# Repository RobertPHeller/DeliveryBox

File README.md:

# Delivery Box -- A lockable box for delivery prople to deliver stuff to.

This is a design for a delivery box -- a lockable box that delivery drivers
can place deliveries into, using one-time codes, where the delivery can be 
securely  housed  until the resident can retrieve  them.  This is to allow for
secure deliveries when noone is home to receive them.  The box will be
lockable and can be secured.  This will make deliveries secure from 
"porch pirates".

- [BoxDesign](BoxDesign/)

- [Circuit](Circuit/)

- [Firmware](DeliveryBoxFirmware/)

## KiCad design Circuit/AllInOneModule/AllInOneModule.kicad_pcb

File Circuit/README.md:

# This is the circuit design

The circuit design uses these parts: 

1. A main board containing an Adafruit ESP32-S3 Feather and connection headers
for a servo  and the  keypad  (there is a  STEMMA/QWIC  connector  for the I2C
connection to the Display Module on th Feather board).  The Adafruit  ESP32-S3
Feather  includes a JST battery  connection and includes a LiPo battery charge
circuit.

2.  A  display  module  with  a  HT16K33   breakout  and  4  dual   14-segment
alphanumberic display modules.

3.  A 12-key keypad board.

4. A high torque metal gear servo will be used to operate a lock.

5. A LiPo battery

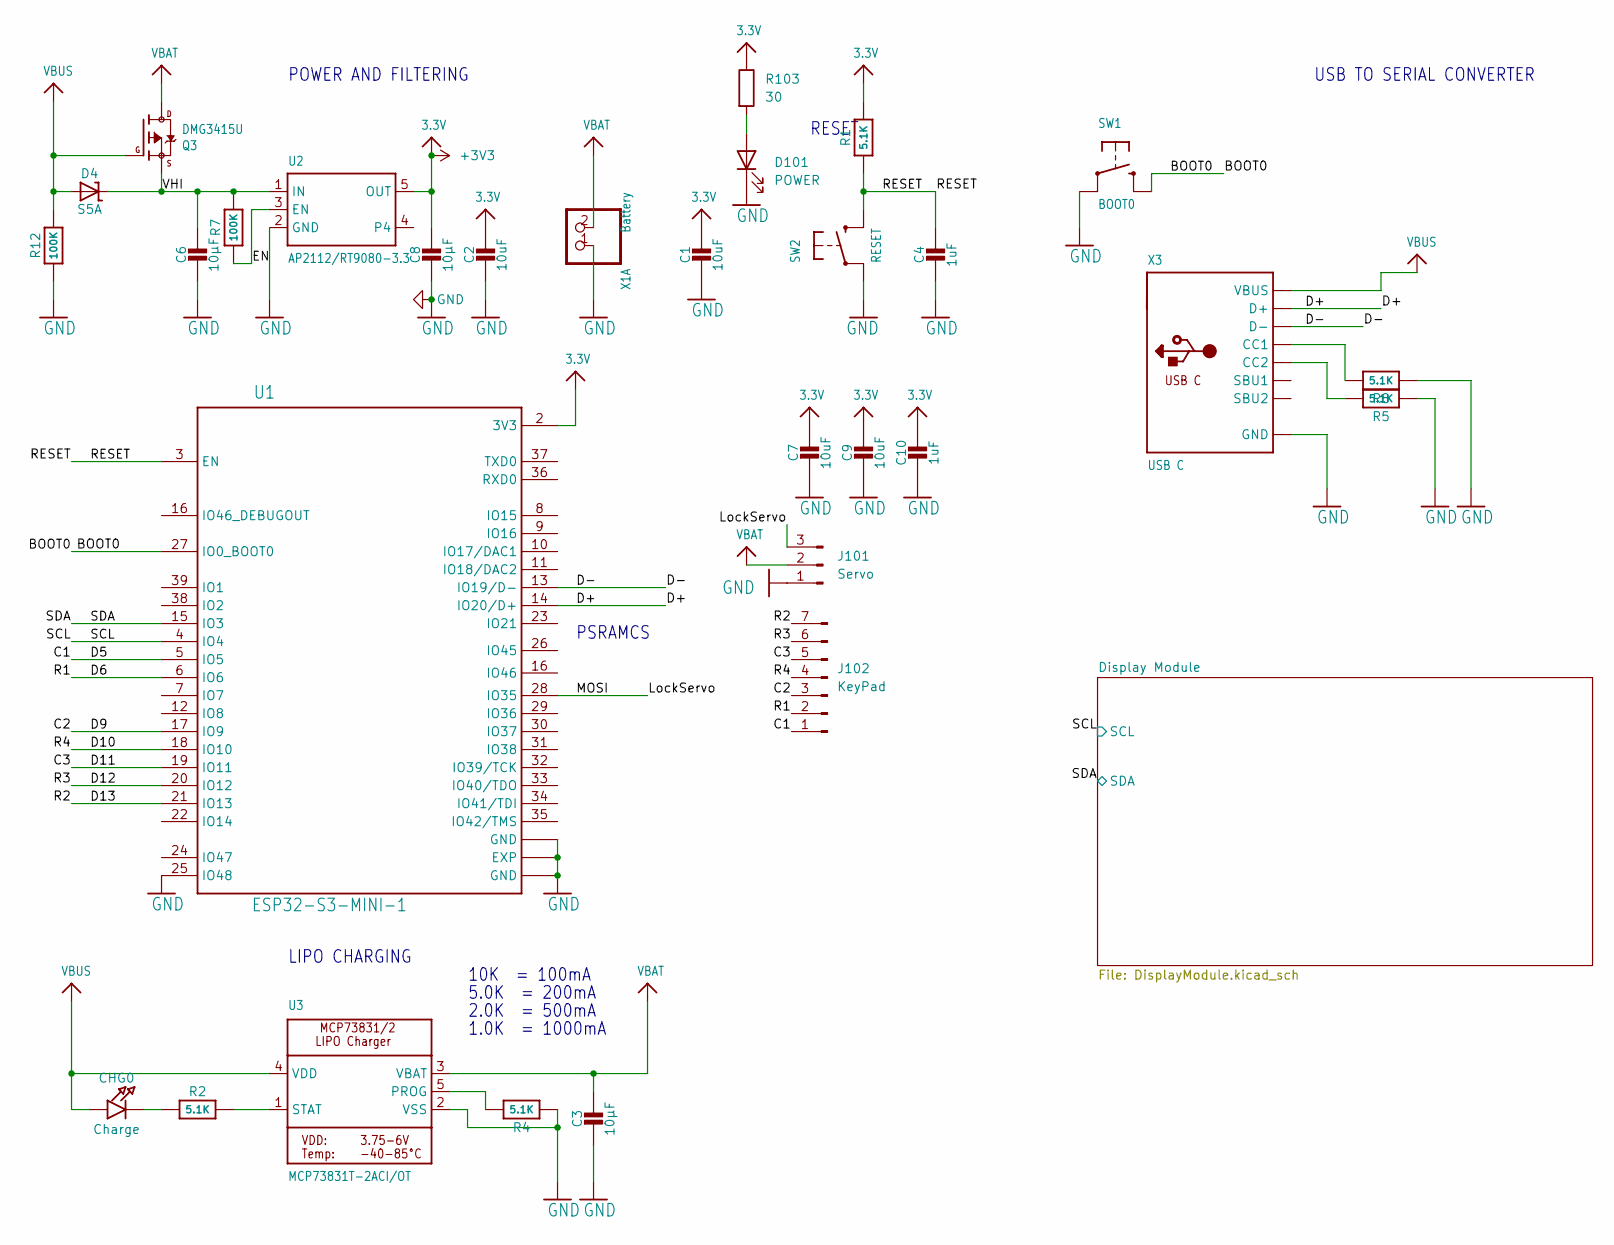
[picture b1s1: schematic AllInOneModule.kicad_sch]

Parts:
C1, C2, C7, C9: 10uF; C_0805_2012Metric; Mouser Part Number 187-CL21A106KQFNFNE
C3, C6, C8: 10µF; C_0805_2012Metric; Mouser Part Number 187-CL21A106KQFNFNE
C4, C10: 1uF; C_0603_1608Metric; Mouser Part Number 80-C0603C105K9PLR
CHG0: Charge; LED_0603_1608Metric; Mouser Part Number 859-LTST-C190KFKT
D4: S5A; S5AE357T; Mouser Part Number 637-S5A
D101: POWER; LED_0603_1608Metric; Mouser Part Number 604-AA1608ZGSK10MAV
J101: Servo; PinHeader_1x03_P2.54mm_Horizontal
J102: KeyPad; PinHeader_1x07_P2.54mm_Horizontal
Q3: DMG3415U; SOT-23-3; Mouser Part Number 621-DMG3415U-7
R1, R2, R4, R5, R8: 5.1K; R_0603_1608Metric; Mouser Part Number 603-RC0603JR-075K1P
R7, R12: 100K; R_0603_1608Metric; Mouser Part Number 603-RT0603DRD07100KL
R103: 30; R_0603_1608Metric; Mouser Part Number 603-AC0603JR-0730RL
SW1: BOOT0; SW_Push_1P1T_NO_CK_KMR2; Mouser Part Number 611-KMR211NGLFS
SW2: RESET; SW_Push_1P1T_NO_CK_KMR2; Mouser Part Number 611-KMR211NGLFS
U1: ESP32-S3-MINI-1; ESP32_S3_WROOM-1; Mouser Part Number 356-ESP32-S3-MINI1N8
U2: AP2112/RT9080-3.3; SOT-23-5; Mouser Part Number 621-AP2112K-3.3TRG1
U3: MCP73831T-2ACI/OT; SOT-23-5; Mouser Part Number 579-MCP73831T-2ACIOT
X1: Battery; JST_PH_S2B-PH-SM4-TB_1x02-1MP_P2.00mm_Horizontal; Mouser Part Number 306-S2BPHSM4TBLFSN
X3: USB C; CONN_USB4930-00-A_GCT; Mouser Part Number 640-USB4930-00-A

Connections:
+3V3: C1.1, C2.1, C7.1, C8.1, C9.1, C10.1, R1.2, R103.1, U1.2 (3V3), U2.5 (OUT); also elsewhere on the board
/BOOT0: SW1.2 (S1), U1.27 (IO0_BOOT0)
/C1: J102.1, U1.5 (IO5)
/C2: J102.3, U1.17 (IO9)
/C3: J102.5, U1.19 (IO11)
/D6: J102.2, U1.6 (IO6)
/D10: J102.4, U1.18 (IO10)
/D12: J102.6, U1.20 (IO12)
/D13: J102.7, U1.21 (IO13)
/D+: U1.14 (IO20/D+), X3.A6 (D+), X3.B6 (D+)
/D-: U1.13 (IO19/D-), X3.A7 (D-), X3.B7 (D-)
/EN: R7.1, U2.3 (EN)
/LockServo: J101.3, U1.28 (IO35)
/RESET: C4.1, R1.1, SW2.2 (S1), U1.3 (EN)
/SCL: U1.4 (IO4); also elsewhere on the board
/SDA: U1.15 (IO3); also elsewhere on the board
/VHI: C6.1, D4.2 (C), Q3.2 (S), R7.2, U2.1 (IN)
GND: C1.2, C2.2, C3.2, C4.2, C6.2, C7.2, C8.2, C9.2, C10.2, D101.1 (K), J101.1, R4.1, R5.1, R8.1, R12.1, SW1.1, SW2.1, U1.1 (GND), U1.25 (IO48), U1.40 (GND), U1.EPad (EXP), U2.2 (GND), U3.2 (VSS), X1.1, X3.A1 (GND), X3.A12 (GND), X3.B1 (GND), X3.B12 (GND); also elsewhere on the board
unnamed: CHG0.1 (C), R2.1
unnamed: D101.2 (A), R103.2
unnamed: R2.2, U3.1 (STAT)
unnamed: R4.2, U3.5 (PROG)
unnamed: R5.2, X3.B5 (CC2)
unnamed: R8.2, X3.A5 (CC1)
VBAT: C3.1, J101.2, Q3.3 (D), U3.3 (VBAT), X1.2
VBUS: CHG0.2 (A), D4.1 (A), Q3.1 (G), R12.2, U3.4 (VDD), X3.A4 (VBUS), X3.A9 (VBUS), X3.B4 (VBUS), X3.B9 (VBUS)

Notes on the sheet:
USB TO SERIAL CONVERTER
LIPO CHARGING
PSRAMCS
5.0K = 200mA
RESET
POWER AND FILTERING
10K = 100mA
2.0K = 500mA
1.0K = 1000mA

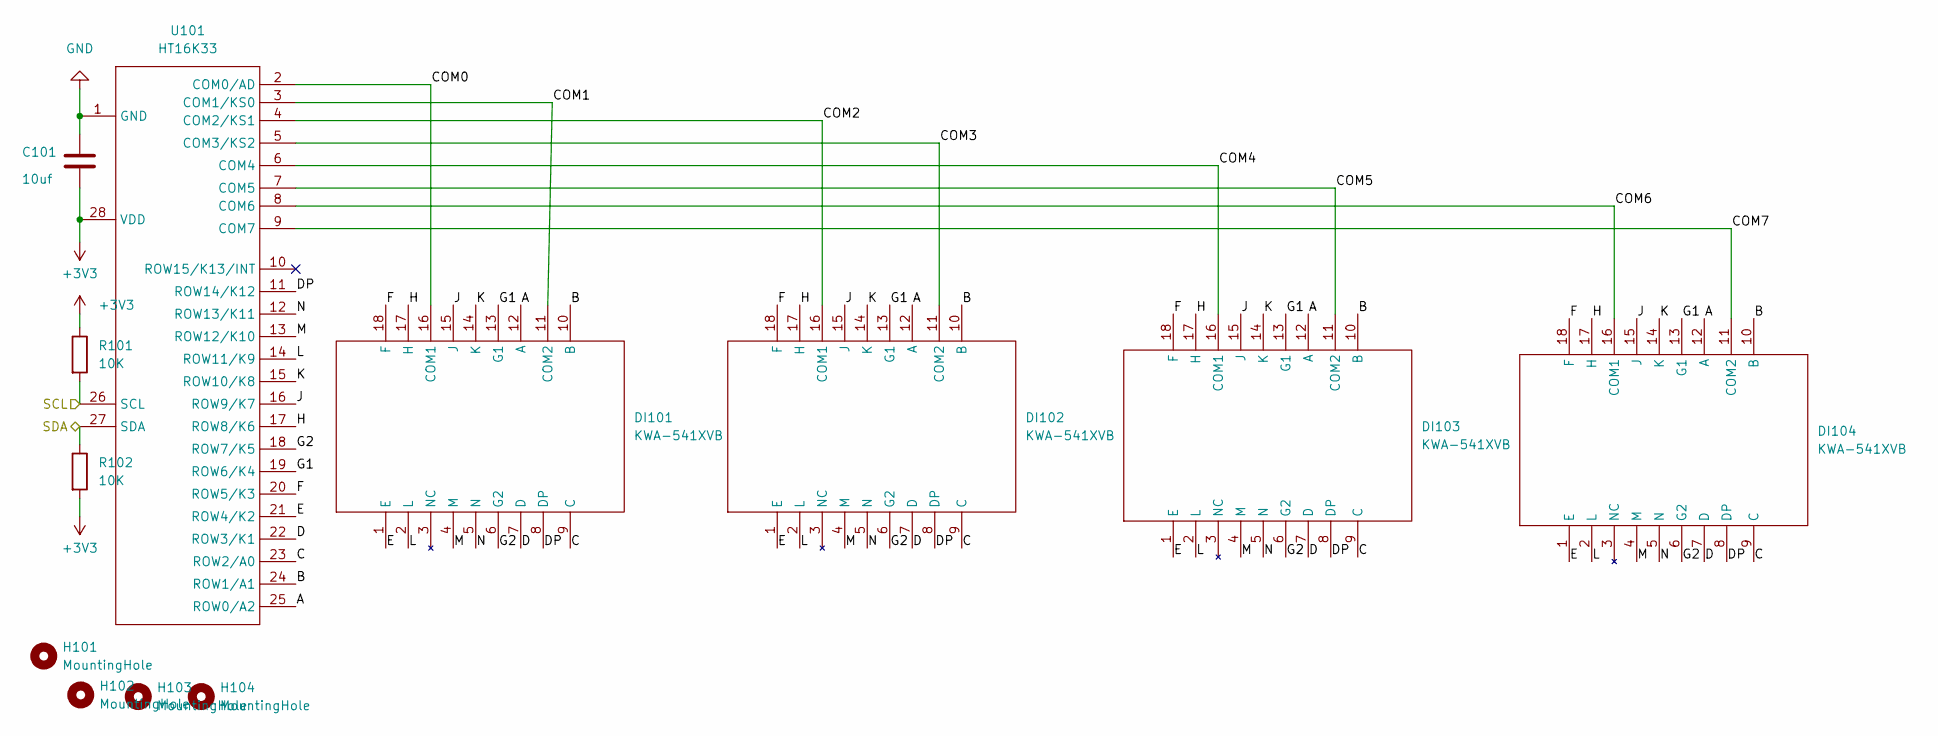
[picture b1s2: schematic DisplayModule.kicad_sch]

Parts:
C101: 10uf; C_0603_1608Metric; Mouser Part Number 963-JMK107ABJ106MA-T
DI101, DI102, DI103, DI104: KWA-541XVB
H101, H102, H103, H104: MountingHole; MountingHole_3.2mm_M3
R101, R102: 10K; R_0603_1608Metric; Mouser Part Number 603-AC0603JR-0710KL
U101: HT16K33; SOIC-28W_7.5x18.7mm_P1.27mm; Manufacturer Part Number HT16K33

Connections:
+3V3: C101.2, R101.1, R102.2, U101.28 (VDD); also elsewhere on the board
/Display Module/A: DI101.12 (A), DI102.12 (A), DI103.12 (A), DI104.12 (A), U101.25 (ROW0/A2)
/Display Module/B: DI101.10 (B), DI102.10 (B), DI103.10 (B), DI104.10 (B), U101.24 (ROW1/A1)
/Display Module/C: DI101.9 (C), DI102.9 (C), DI103.9 (C), DI104.9 (C), U101.23 (ROW2/A0)
/Display Module/COM0: DI101.16 (COM1), U101.2 (COM0/AD)
/Display Module/COM1: DI101.11 (COM2), U101.3 (COM1/KS0)
/Display Module/COM2: DI102.16 (COM1), U101.4 (COM2/KS1)
/Display Module/COM3: DI102.11 (COM2), U101.5 (COM3/KS2)
/Display Module/COM4: DI103.16 (COM1), U101.6 (COM4)
/Display Module/COM5: DI103.11 (COM2), U101.7 (COM5)
/Display Module/COM6: DI104.16 (COM1), U101.8 (COM6)
/Display Module/COM7: DI104.11 (COM2), U101.9 (COM7)
/Display Module/D: DI101.7 (D), DI102.7 (D), DI103.7 (D), DI104.7 (D), U101.22 (ROW3/K1)
/Display Module/DP: DI101.8 (DP), DI102.8 (DP), DI103.8 (DP), DI104.8 (DP), U101.11 (ROW14/K12)
/Display Module/E: DI101.1 (E), DI102.1 (E), DI103.1 (E), DI104.1 (E), U101.21 (ROW4/K2)
/Display Module/F: DI101.18 (F), DI102.18 (F), DI103.18 (F), DI104.18 (F), U101.20 (ROW5/K3)
/Display Module/G1: DI101.13 (G1), DI102.13 (G1), DI103.13 (G1), DI104.13 (G1), U101.19 (ROW6/K4)
/Display Module/G2: DI101.6 (G2), DI102.6 (G2), DI103.6 (G2), DI104.6 (G2), U101.18 (ROW7/K5)
/Display Module/H: DI101.17 (H), DI102.17 (H), DI103.17 (H), DI104.17 (H), U101.17 (ROW8/K6)
/Display Module/J: DI101.15 (J), DI102.15 (J), DI103.15 (J), DI104.15 (J), U101.16 (ROW9/K7)
/Display Module/K: DI101.14 (K), DI102.14 (K), DI103.14 (K), DI104.14 (K), U101.15 (ROW10/K8)
/Display Module/L: DI101.2 (L), DI102.2 (L), DI103.2 (L), DI104.2 (L), U101.14 (ROW11/K9)
/Display Module/M: DI101.4 (M), DI102.4 (M), DI103.4 (M), DI104.4 (M), U101.13 (ROW12/K10)
/Display Module/N: DI101.5 (N), DI102.5 (N), DI103.5 (N), DI104.5 (N), U101.12 (ROW13/K11)
/SCL: R101.2, U101.26 (SCL); also elsewhere on the board
/SDA: R102.1, U101.27 (SDA); also elsewhere on the board
GND: C101.1, U101.1 (GND); also elsewhere on the board

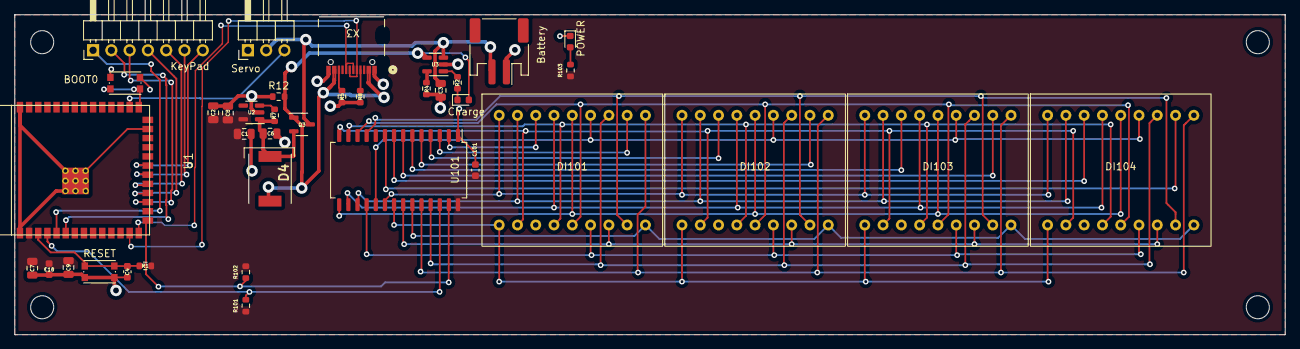
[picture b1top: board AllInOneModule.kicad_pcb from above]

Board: 2 copper layers, 176.5 x 44.5 mm, 42 parts (0 on the bottom side), 49 nets.

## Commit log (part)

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2026-06-16 Initial commit.
2026-06-16 Starting on box design.
2026-06-17 Refactor firmare and build infrastructure.
2026-06-18 Create Display Module with Fritzing
2026-06-18 Working on Firmware.
2026-06-18 Snapshot commit.
2026-06-19 Add main control module.
2026-06-19 Firmware initial version complete.
2026-06-19 Set LaTeX paper size to letter and enable batchmode in Doxyfile.
2026-06-19 Documentation updates.
2026-06-20 Documentation.
2026-06-20 Wood part completed.
2026-06-25 Complete box design.
2026-06-25 Design PCB for display module.
2026-06-27 Box design almost done.
2026-06-27 PCB Completed.
2026-06-27 Add Bluetooth WiFi config.
2026-06-30 Add Styled Delivery Box App.
2026-06-30 Updated Fritzing version of Display Module.
